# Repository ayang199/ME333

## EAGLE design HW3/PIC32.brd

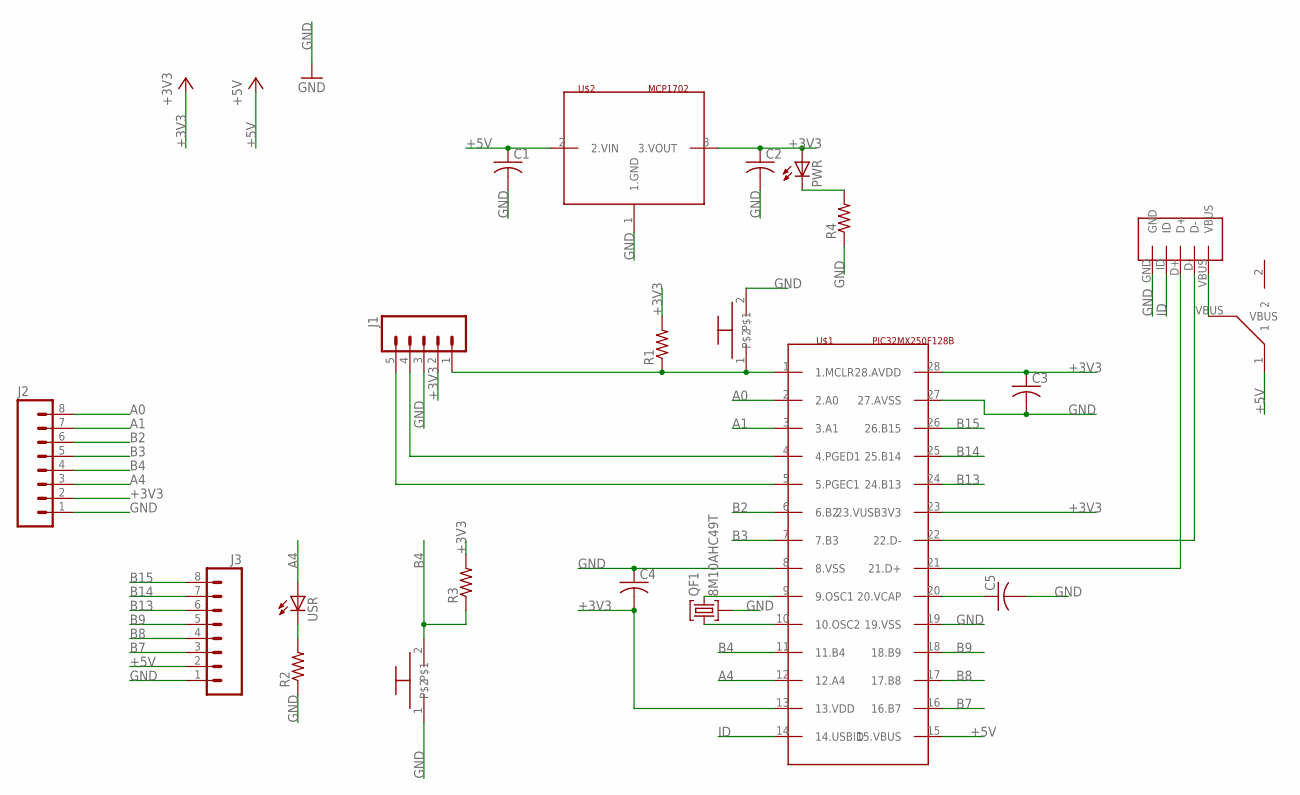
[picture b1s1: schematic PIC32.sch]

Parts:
C1, C2, C3, C4: C-US025-024X044; C025-024X044
C5: C-US025-030X050; C025-030X050
J1: M05PTH; 1X05
J2, J3: M08; 1X08_ROUND
PWR: LED3MM
QF1: 8M10AHC49T; HC49U
R1, R2, R3, R4: R-US_0207/10; 0207/10
RESET: PUSHBUTTON
U$1: PIC32MX250F128B; DIL28-3
U$2: MCP1702; TO92-EBC
U$4: USB; USB-MB-H
U$6: SLIDESWITCH
USER: PUSHBUTTON
USR: LED3MM

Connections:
+3V3: C2.1, C3.1, C4.2, J1.2, J2.2, PWR.A, R1.2, R3.2, U$1.13 (13.VDD), U$1.23 (23.VUSB3V3), U$1.28 (28.AVDD), U$2.3 (3.VOUT)
+5V: C1.1, J3.2, U$1.15 (15.VBUS), U$2.2 (2.VIN), U$6.1
A0: J2.8, U$1.2 (2.A0)
A1: J2.7, U$1.3 (3.A1)
A4: J2.3, U$1.12 (12.A4), USR.A
B2: J2.6, U$1.6 (6.B2)
B3: J2.5, U$1.7 (7.B3)
B4: J2.4, R3.1, U$1.11 (11.B4), USER.2
B7: J3.3, U$1.16 (16.B7)
B8: J3.4, U$1.17 (17.B8)
B9: J3.5, U$1.18 (18.B9)
B13: J3.6, U$1.24 (24.B13)
B14: J3.7, U$1.25 (25.B14)
B15: J3.8, U$1.26 (26.B15)
GND: C1.2, C2.2, C3.2, C4.1, C5.2, J1.3, J2.1, J3.1, QF1.2, R2.1, R4.1, RESET.2, U$1.8 (8.VSS), U$1.19 (19.VSS), U$1.27 (27.AVSS), U$2.1 (1.GND), U$4.GND, USER.1
ID: U$1.14 (14.USBID), U$4.ID
unnamed: J1.1, R1.1, RESET.1, U$1.1 (1.MCLR)
unnamed: J1.4, U$1.4 (4.PGED1)
unnamed: J1.5, U$1.5 (5.PGEC1)
unnamed: QF1.1, U$1.10 (10.OSC2)
unnamed: C5.1, U$1.20 (20.VCAP)
unnamed: R2.2, USR.K (C)
unnamed: U$4.VBUS, U$6.VBUS
unnamed: QF1.3, U$1.9 (9.OSC1)
unnamed: U$1.21 (21.D+), U$4.D+
unnamed: U$1.22 (22.D-), U$4.D-
unnamed: PWR.K (C), R4.2

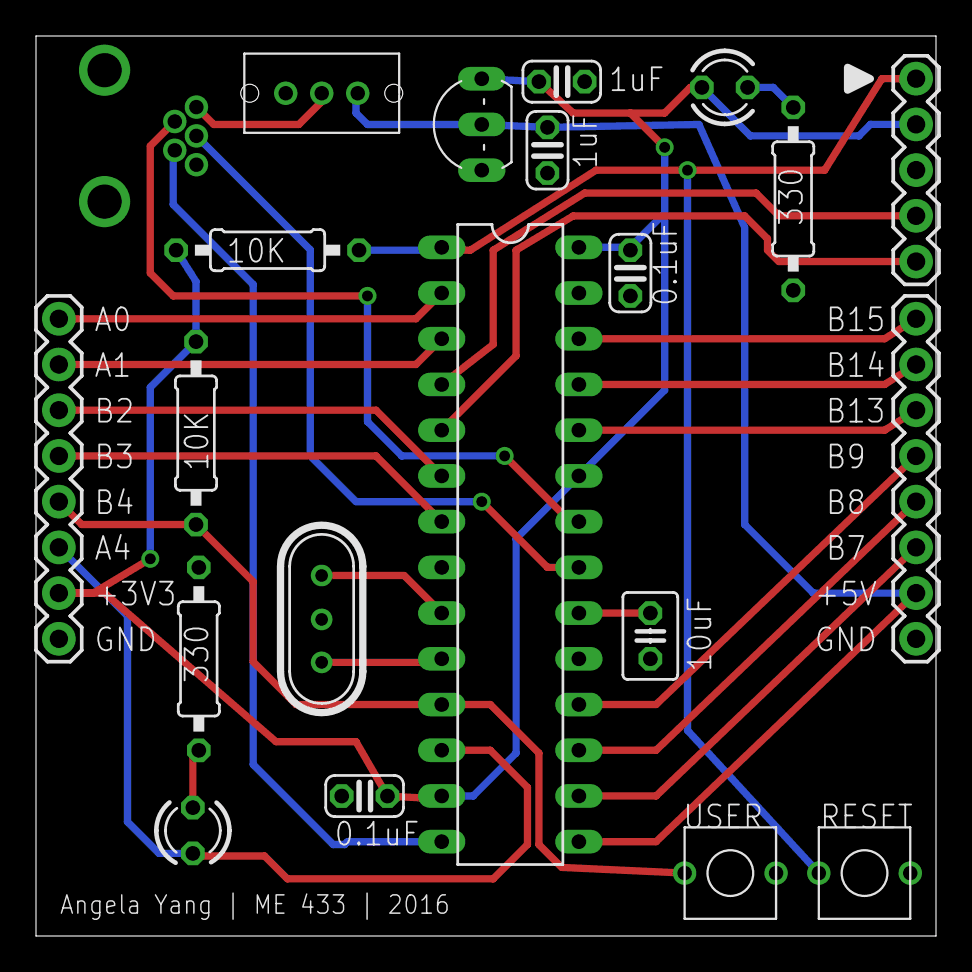
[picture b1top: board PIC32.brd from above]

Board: 2 copper layers, 50.0 x 50.0 mm, 21 parts (0 on the bottom side), 27 nets.

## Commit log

2016-04-01 HW1 New Project
2016-04-01 DEVCFG and setup
    Set the DEVCFG registers, included xc.h and set up the void main()
    function
2016-04-01 Delay function and toggle
    Added a delay function and toggle function. The toggle function toggles
    A4 (the LED) while the delay function waits 1/1000 seconds between each
    toggle. Copied from ME333 assignment.
2016-04-01 Pin initialization
    Cleared and configured output pin
2016-04-01 Update registers
    Updated DEVCFG registers using "Configuration Bits" window in MPLAB
2016-04-03 Updated using template
2016-04-03 Breadboard and circuit diagram
2016-04-03 Added files via upload
2016-04-03 Edits via template
    Made edits according to the template. Everything works except the
    timing.
2016-04-04 Final Code Done
2016-04-10 Organized folders
2016-04-10 Library and schematic
2016-04-10 Added header pins
2016-04-14 Completed board
    Ready to be checked before order
2016-04-23 Started SPI code
2016-04-23 Final HW1
2016-04-23 SPI working
2016-04-23 SPI complete
2016-04-24 Started I2C code
2016-05-01 i2c still not working :(
2016-05-03 can read IMU
    Able to read the WHO_AM_I register from the IMU but still unable to read
    anything from the pin expander
2016-05-03 HW 4 Finished
    It works!!!
2016-05-08 i2c Read/Write Functions work
2016-05-08 IMU draft
    Needs debugging
2016-05-08 HW5 Complete
2016-05-08 HW6 Data Displayed
    Temp, gyro, and accel data printed on LCD screen
2016-05-08 HW6 Complete
2016-06-03 HW 9 done
2016-06-05 Android Camera works
2016-06-05 HW8 Done
2016-06-05 HW10 done
    Tire needs to be slightly adjusted
2016-06-05 HW13 half done
    Phone detects PIC, writes and reads value
2016-06-05 Seekbar added
    Seekbar sends value to PIC, which displays on screen. Does not write
    over original value though.
2016-06-05 PWM works
    PIC can read qq value from computer and change duty cycle
2016-06-05 HW13 Done
2016-06-05 Refining Camera app
2016-06-07 HW15 (PIC final code) Done
2016-06-07 HW15 updated
2016-06-07 HW14 sort of done
    Android senses angle and position of line. Need to figure out what to do
    with data (how to adjust PWM). Also need to convert to color
2016-06-08 Everything works kind of
    Need to test/adjust on mat once new housing is laser cut and wheels are
    printed
2016-06-09 Robot works! (Video uploaded)
2016-06-09 HW7 - Mouse
2016-06-09 HW11 - Laser cut box
2016-06-09 Finished box
